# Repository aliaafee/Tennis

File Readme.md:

# Tennis

Pong like two player game that runs on ATtiny85 Microcontroller, with SSD1306 OLED (128x64 0.96 inch) display. Input with potentiometers, one for each player, and four buttons.

## Preamble

### Setup ArduinoISP

* Build and Upload ArduinoISP Program to an Ardunio UNO / Nano or other appropriate board.
* Add Additional Board Manager URL for ATtiny85 (File > Preferences): https://raw.githubusercontent.com/damellis/attiny/ide-1.6.x-boards-manager/package_damellis_attiny_index.json
* Install Attiny Package from Boards Manager

### Prepare ATtiny85 for Programming

* Hookup Attiny to Arduino ISP (Pin1 -> D10, Pin4 -> GND, Pin5 -> D11, Pin6 -> D12, Pin7 -> D13, Pin8 -> GND)
* Select Board : ATtiny25/45/85
* Select Processor: Attiny85
* Select Clock: Internal 8MHz
* Select port where ArduinoISP is pulgged int.
* Select programmer: Arduino ISP
* Burn Bootloader

## Build and Upload the Project

* Install PlatformIO
* Install required depenencies `pio lib install`
* Update `board` and `upload_port` to appropriate values in `platformio.ini`
* Build `pio run`
* Upload to device `pio run -t upload`

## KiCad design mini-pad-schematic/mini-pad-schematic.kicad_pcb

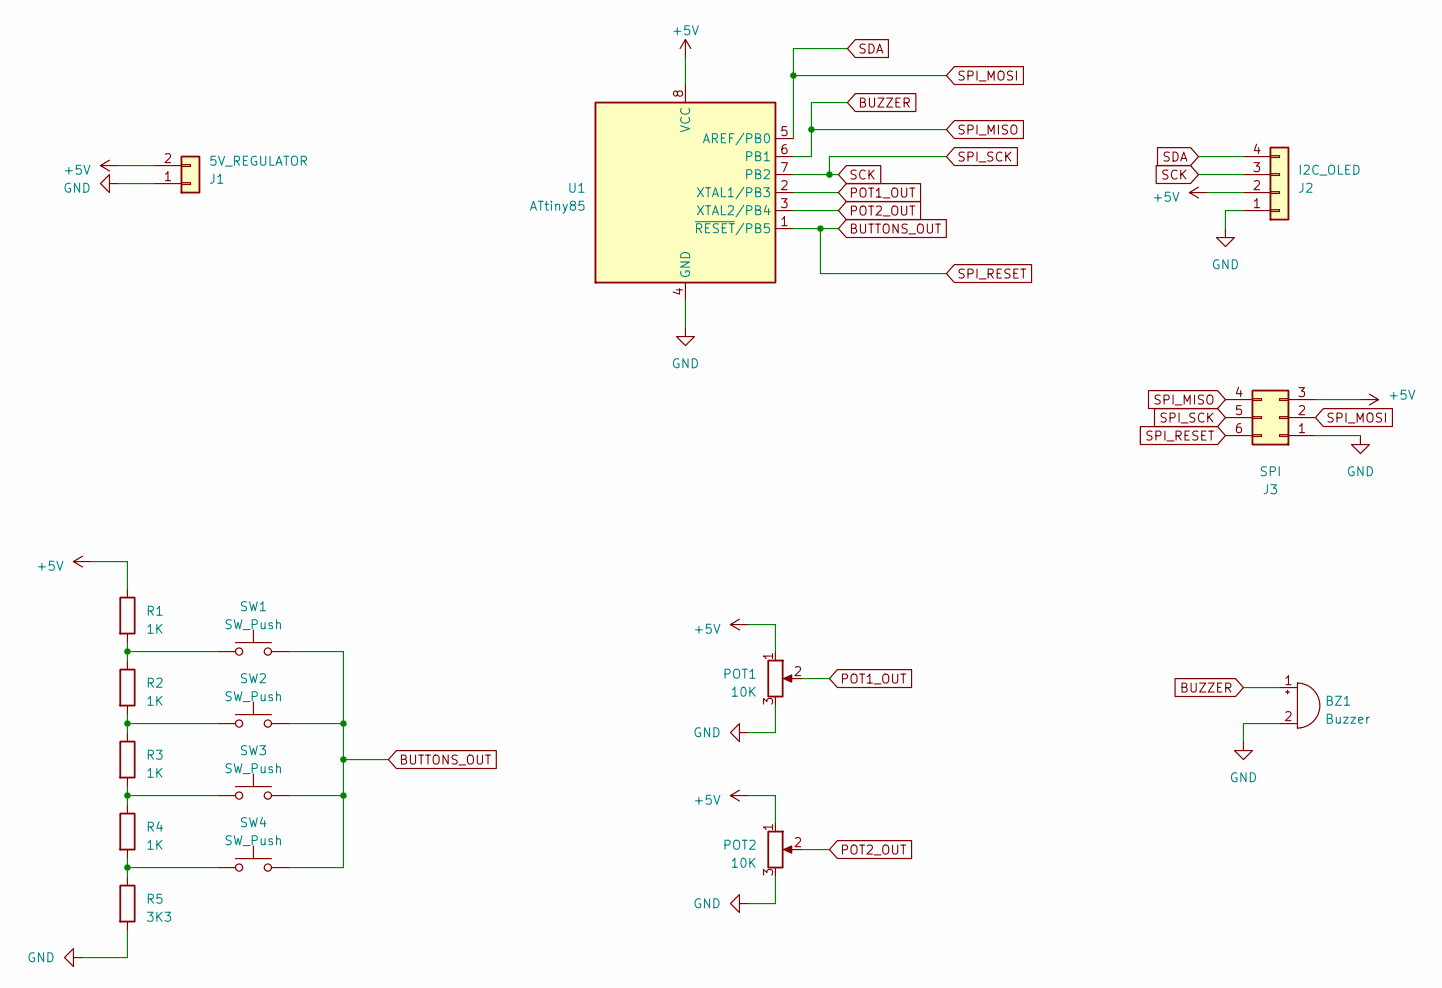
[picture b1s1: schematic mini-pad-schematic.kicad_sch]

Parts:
BZ1: Buzzer; Buzzer_12x9.5RM7.6
J1: 5V_REGULATOR; PinHeader_1x02_P2.54mm_Vertical
J2: I2C_OLED; PinSocket_1x04_P2.54mm_Vertical
J3: SPI; PinSocket_2x03_P2.54mm_Vertical
POT1, POT2: 10K; Potentiometer_Alpha_RD901F-40-00D_Single_Vertical
R1, R2, R3, R4: 1K; R_Axial_DIN0207_L6.3mm_D2.5mm_P7.62mm_Horizontal
R5: 3K3; R_Axial_DIN0207_L6.3mm_D2.5mm_P7.62mm_Horizontal
SW1, SW2, SW3, SW4: SW_Push; SW_PUSH_6mm_H5mm
U1: ATtiny85; DIP-8_W7.62mm

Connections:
+5V: J1.2, J2.2, J3.3, POT1.1, POT2.1, R1.1, U1.8 (VCC)
BUTTONS_OUT: J3.6, SW1.2, SW2.2, SW3.2, SW4.2, U1.1 (~RESET/PB5)
BUZZER: BZ1.1 (-), J3.4, U1.6 (PB1)
GND: BZ1.2 (+), J1.1, J2.1, J3.1, POT1.3, POT2.3, R5.2, U1.4 (GND)
unnamed: R1.2, R2.1, SW1.1
unnamed: R2.2, R3.1, SW2.1
unnamed: R3.2, R4.1, SW3.1
unnamed: R4.2, R5.1, SW4.1
POT1_OUT: POT1.2, U1.2 (XTAL1/PB3)
POT2_OUT: POT2.2, U1.3 (XTAL2/PB4)
SCK: J2.3, J3.5, U1.7 (PB2)
SDA: J2.4, J3.2, U1.5 (AREF/PB0)

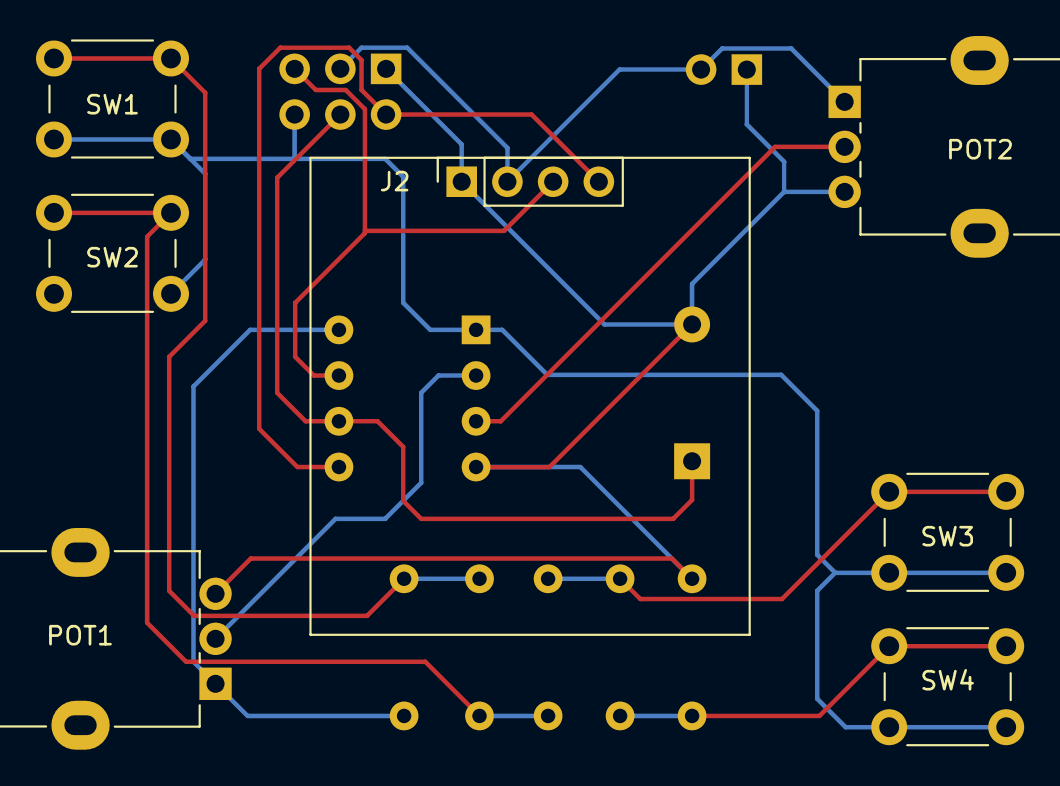
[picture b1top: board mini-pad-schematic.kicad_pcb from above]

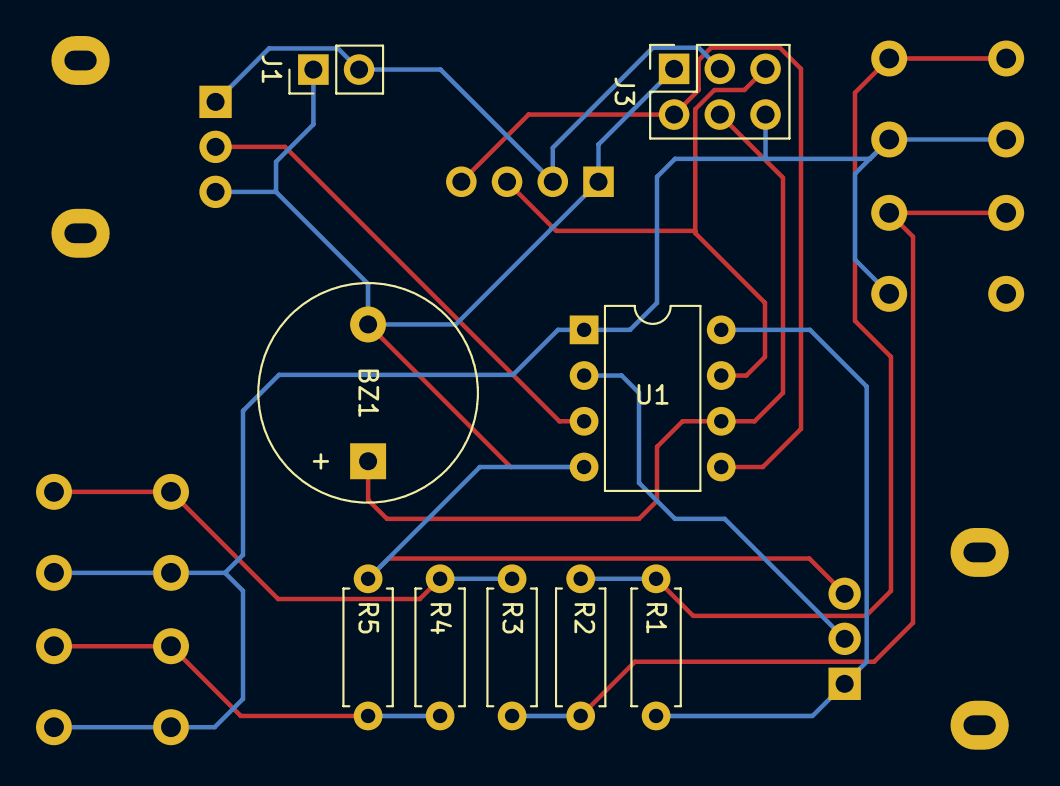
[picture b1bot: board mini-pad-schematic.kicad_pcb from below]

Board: 2 copper layers, 16 parts (9 on the bottom side), 12 nets.

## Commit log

2023-04-23 Wrote the Readme.md
2023-04-23 Added Schematic
2023-04-23 Added photos
2023-04-25 Added buzzer
2023-05-05 update the pcb design
2023-06-01 Switched to custom stripped down oled library which allows a 24% savings in Flash memory usage
2023-06-01 Some changes
